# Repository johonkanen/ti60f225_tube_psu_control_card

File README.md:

# Ti60F225 control card

An FPGA control card for the tube_power_5_1 power board, built around an Efinix Titanium Ti60F225C4, designed in
KiCad 10. It is a conversion of the Agilex 3 control card (`~/dev/ti60f225_control_card`, GitHub
`agilex3_control_card`): same outline, 2×25 1.27 mm power-board header and JTAG header positions.

**Status: phase 4 of the conversion done (2026-10-30).** The schematic is converted to the Ti60F225 (ERC clean,
netlist checked by `tools/check_schematic.py`), and its FPGA ball assignment passes Efinity's Interface Designer
check and a stub compile with SPI active x4 (`efinity/pinplan/run.sh --compile`, `reference/pin_assignment.csv`). The board
(`hardware/control_card.kicad_pcb`) is still the Agilex 3 layout. Plan, decisions and remaining steps:
[`CONVERSION_PLAN.md`](CONVERSION_PLAN.md); device requirements: [`docs/ti60_requirements.md`](docs/ti60_requirements.md).

## Board

Copper layers of `hardware/control_card.kicad_pcb`, plotted by GitHub Actions on every board change
([kicad-board-plots](https://github.com/johonkanen/kicad-board-plots)).

<!-- board-plots:start -->
<!-- Generated by kicad-board-plots; edits between these markers are overwritten. -->

Copper layers of `hardware/control_card.kicad_pcb` in stack order, without silkscreen. Plotted by [kicad-board-plots](https://github.com/johonkanen/kicad-board-plots) on each board change; the images live on the `renders` branch.

<table>
<tr>
<td align="center"><br><b>F.Cu: signal (top)</b></td>
<td align="center"><br><b>In1.Cu: GND plane</b></td>
</tr>
<tr>
<td align="center"><br><b>In2.Cu: signal, +1V8 pour</b></td>
<td align="center"><br><b>In3.Cu: +0V95, +3V3 planes</b></td>
</tr>
<tr>
<td align="center"><br><b>In4.Cu: GND plane</b></td>
<td align="center"><br><b>B.Cu: signal, SW_3V3, SW_1V8, +0V95, GND, SW_0V95 and 3 more pours (bottom, seen from the top)</b></td>
</tr>
</table>

<!-- board-plots:end -->

## Repository layout

| Path | Contents |
|---|---|
| `hardware/` | KiCad project (`control_card.kicad_pro`), sheets, project libraries, JLCPCB design rules |
| `reference/ti60f225_pinout.csv` | All 225 Ti60F225 balls: pad, bank, HVIO/HSIO type, configuration function, LVDS pair, clock region |
| `reference/` | Power-board header pinout, ADC mux channel table, JLC part cache, the Agilex pin list (for net names) |
| `docs/` | JLCPCB production checklist |
| `tools/jlc/` | Submodule [jlc-tools](https://github.com/johonkanen/jlc-tools): JLC part search, stock check, BOM/CPL and Gerber export |

Clone with `git clone --recursive`, or run `git submodule update --init` after cloning.

## License

[MIT](LICENSE).

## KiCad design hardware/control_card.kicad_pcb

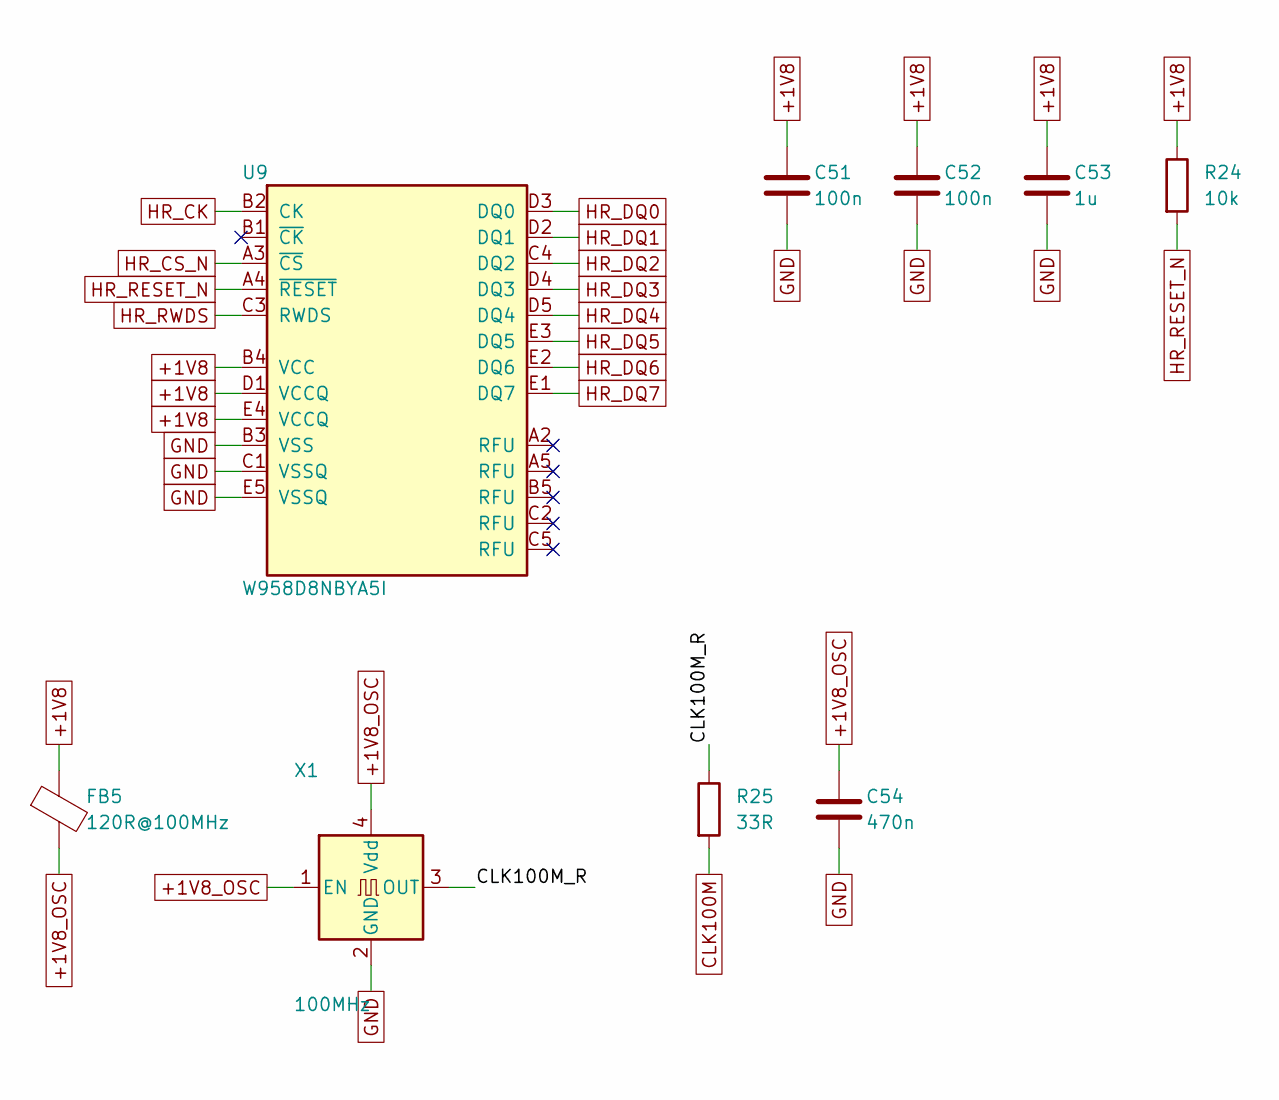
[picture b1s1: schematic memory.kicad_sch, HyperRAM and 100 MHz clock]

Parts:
C51, C52: 100n; C_0402_1005Metric; MPN CL05B104KO5NNNC; LCSC C1525
C53: 1u; C_0402_1005Metric; MPN CL05A105KA5NQNC; LCSC C52923
C54: 470n; C_0402_1005Metric; MPN CL05A474KP5NNNC; LCSC C47339
FB5: 120R@100MHz; L_0603_1608Metric; MPN BLM18PG121SN1D; LCSC C14709
R24: 10k; R_0402_1005Metric; MPN 0402WGF1002TCE; LCSC C25744
R25: 33R; R_0402_1005Metric; MPN 0402WGF330JTCE; LCSC C25105
U9: W958D8NBYA5I; BGA-24_6x8mm_Layout5x5_P1.0mm_CY0.5; MPN W958D8NBYA5I; LCSC C7420405
X1: 100MHz; Oscillator_SMD_Abracon_ASE-4Pin_3.2x2.5mm; MPN OT3225100MJBA4SL; LCSC C4353707

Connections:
+1V8: C51.1, C52.1, C53.1, FB5.1, R24.1, U9.B4 (VCC), U9.D1 (VCCQ), U9.E4 (VCCQ); also elsewhere on the board
+1V8_OSC: C54.1, FB5.2, X1.1 (EN), X1.4 (Vdd)
/HyperRAM and clock/CLK100M_R: R25.1, X1.3 (OUT)
CLK100M: R25.2; also elsewhere on the board
GND: C51.2, C52.2, C53.2, C54.2, U9.B3 (VSS), U9.C1 (VSSQ), U9.E5 (VSSQ), X1.2 (GND); also elsewhere on the board
HR_CK: U9.B2 (CK); also elsewhere on the board
HR_CS_N: U9.A3 (~CS); also elsewhere on the board
HR_DQ0: U9.D3 (DQ0); also elsewhere on the board
HR_DQ1: U9.D2 (DQ1); also elsewhere on the board
HR_DQ2: U9.C4 (DQ2); also elsewhere on the board
HR_DQ3: U9.D4 (DQ3); also elsewhere on the board
HR_DQ4: U9.D5 (DQ4); also elsewhere on the board
HR_DQ5: U9.E3 (DQ5); also elsewhere on the board
HR_DQ6: U9.E2 (DQ6); also elsewhere on the board
HR_DQ7: U9.E1 (DQ7); also elsewhere on the board
HR_RESET_N: R24.2, U9.A4 (~RESET); also elsewhere on the board
HR_RWDS: U9.C3 (RWDS); also elsewhere on the board

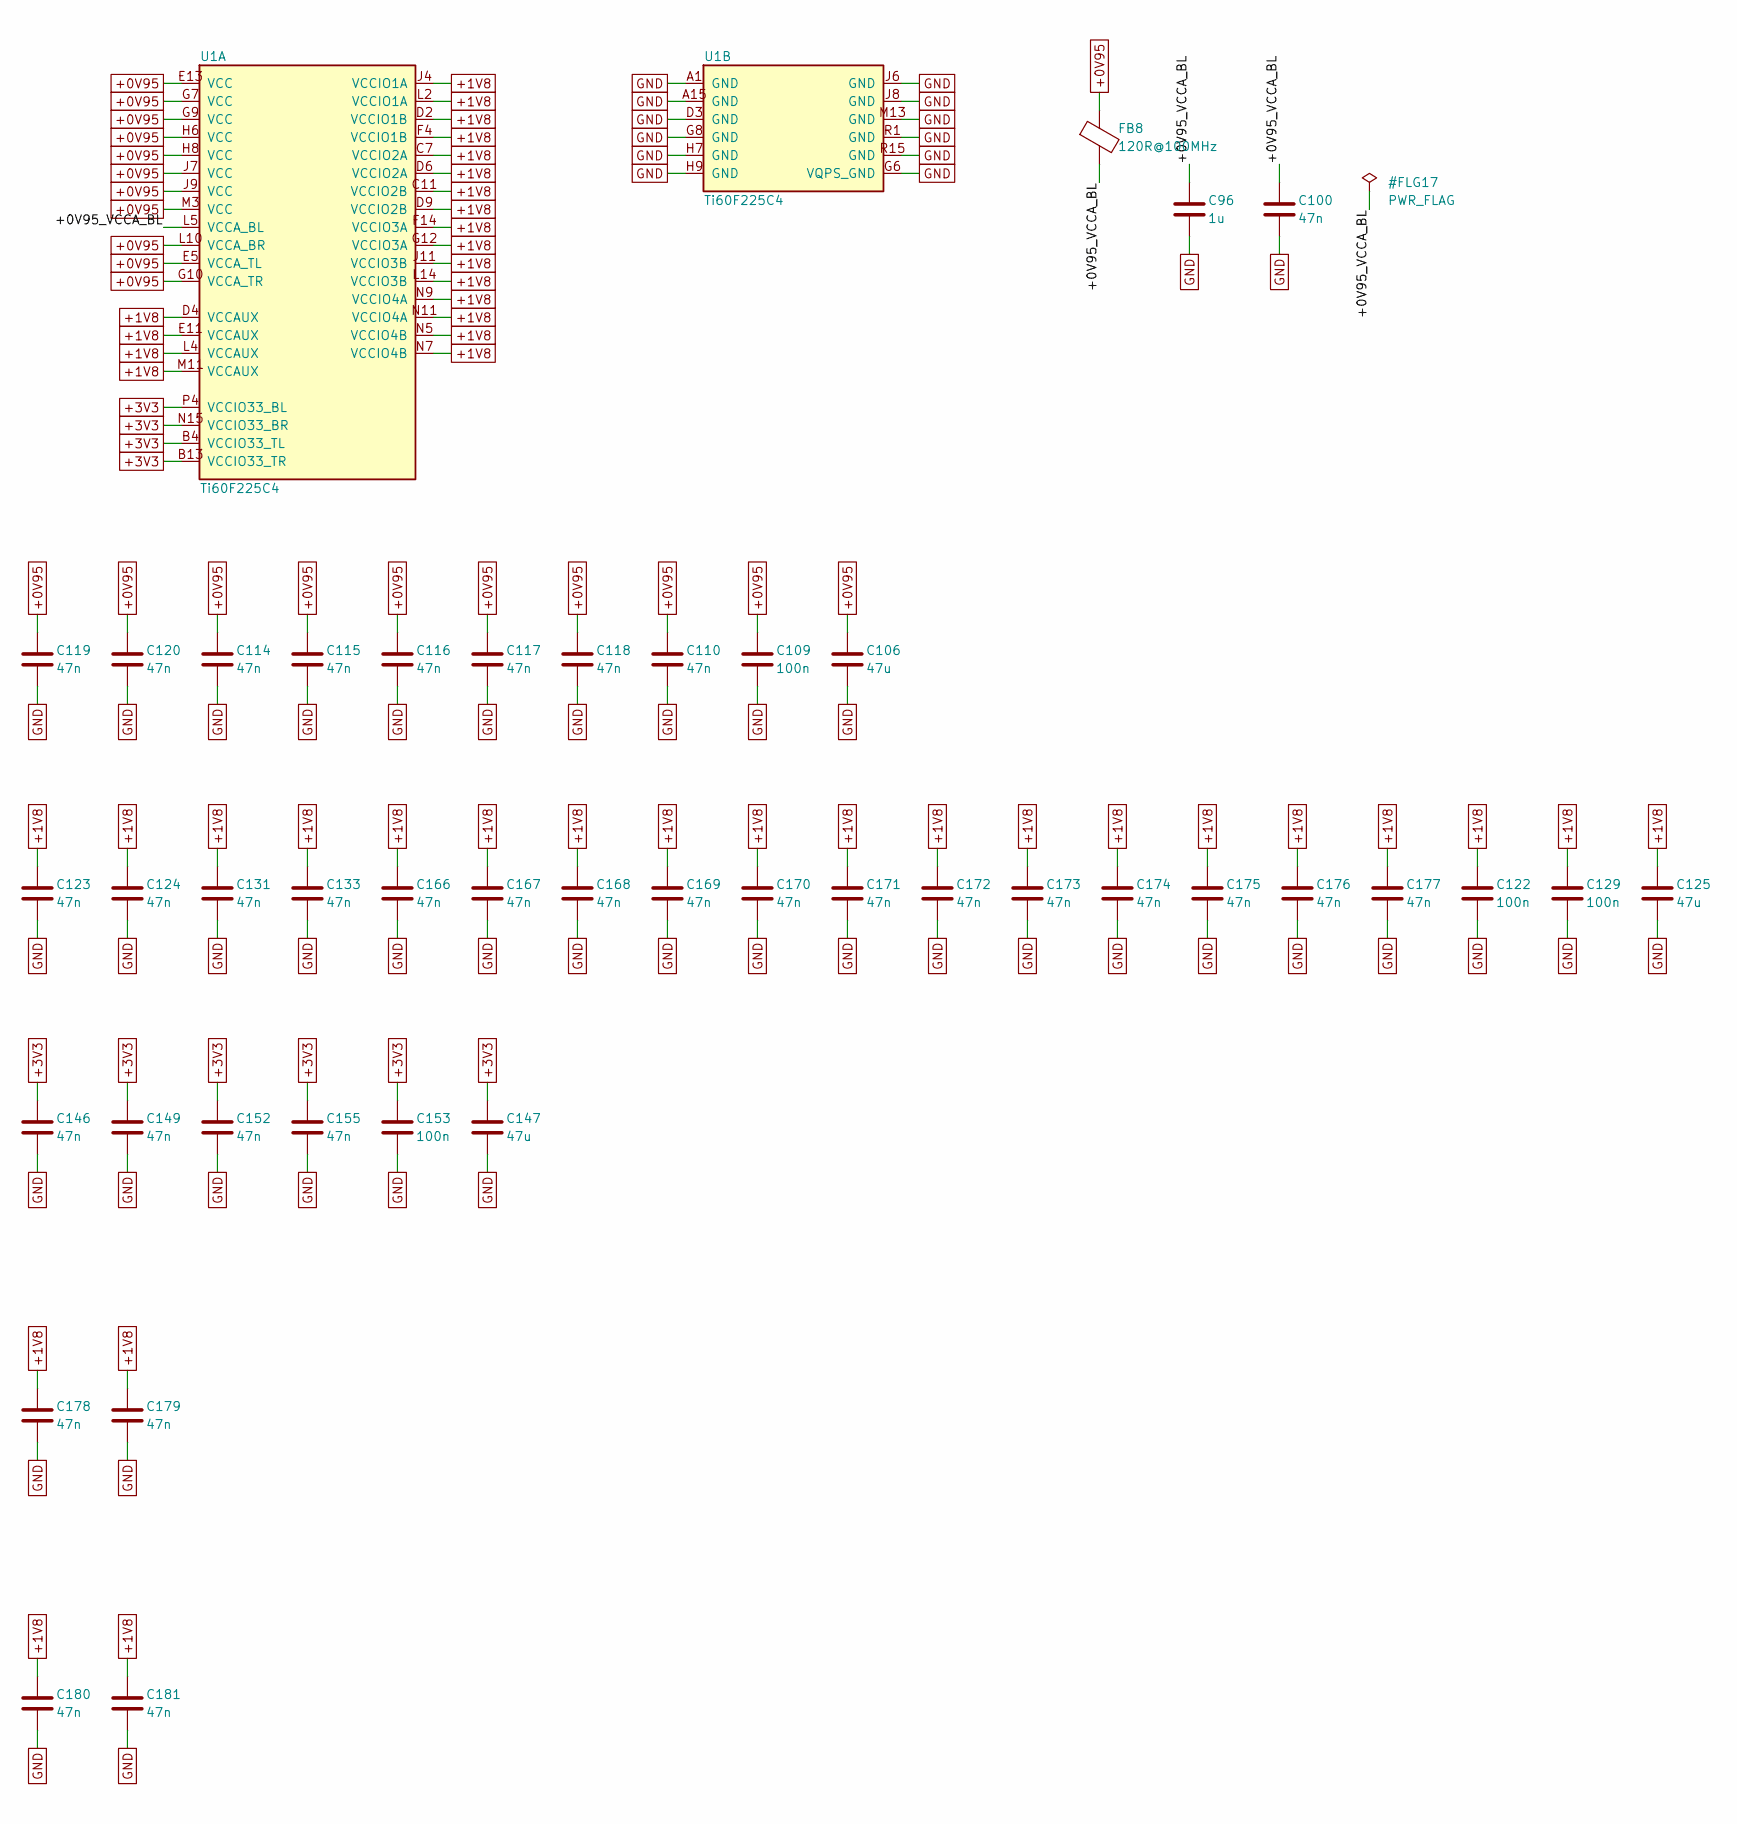
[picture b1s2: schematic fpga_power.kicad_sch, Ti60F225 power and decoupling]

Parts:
C96: 1u; C_0201_0603Metric; MPN CL03A105MQ3CSNC; LCSC C170152
C100, C110, C114, C115, C116, C117, C118, C119, C120, C123, C124, C131, C133, C146, C149, C152, C155, C166, C167, C168, C169, C170, C171, C172, C173, C174, C175, C176, C177, C178, C179, C180, C181: 47n; C_0201_0603Metric; MPN GRM033R60J473KE19D; LCSC C85925
C106, C125, C147: 47u; C_0603_1608Metric; MPN GRM188R60J476ME15D; LCSC C140782
C109, C122, C129, C153: 100n; C_0201_0603Metric; MPN CL03A104KP3NNNC; LCSC C49062
FB8: 120R@100MHz; L_0603_1608Metric; MPN BLM18PG121SN1D; LCSC C14709
U1: Ti60F225C4; Efinix_F225; MPN Ti60F225C4

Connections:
+0V95: C106.1, C109.1, C110.1, C114.1, C115.1, C116.1, C117.1, C118.1, C119.1, C120.1, FB8.1, U1.E5 (VCCA_TL), U1.E13 (VCC), U1.G7 (VCC), U1.G9 (VCC), U1.G10 (VCCA_TR), U1.H6 (VCC), U1.H8 (VCC), U1.J7 (VCC), U1.J9 (VCC), U1.L10 (VCCA_BR), U1.M3 (VCC); also elsewhere on the board
+1V8: C122.1, C123.1, C124.1, C125.1, C129.1, C131.1, C133.1, C166.1, C167.1, C168.1, C169.1, C170.1, C171.1, C172.1, C173.1, C174.1, C175.1, C176.1, C177.1, C178.1, C179.1, C180.1, C181.1, U1.C7 (VCCIO2A), U1.C11 (VCCIO2B), U1.D2 (VCCIO1B), U1.D4 (VCCAUX), U1.D6 (VCCIO2A), U1.D9 (VCCIO2B), U1.E11 (VCCAUX), U1.F4 (VCCIO1B), U1.F14 (VCCIO3A), U1.G12 (VCCIO3A), U1.J4 (VCCIO1A), U1.J11 (VCCIO3B), U1.L2 (VCCIO1A), U1.L4 (VCCAUX), U1.L14 (VCCIO3B), U1.M11 (VCCAUX), U1.N5 (VCCIO4B), U1.N7 (VCCIO4B), U1.N9 (VCCIO4A), U1.N11 (VCCIO4A); also elsewhere on the board
+3V3: C146.1, C147.1, C149.1, C152.1, C153.1, C155.1, U1.B4 (VCCIO33_TL), U1.B13 (VCCIO33_TR), U1.N15 (VCCIO33_BR), U1.P4 (VCCIO33_BL); also elsewhere on the board
/FPGA power/+0V95_VCCA_BL: C96.1, C100.1, FB8.2, U1.L5 (VCCA_BL)
GND: C96.2, C100.2, C106.2, C109.2, C110.2, C114.2, C115.2, C116.2, C117.2, C118.2, C119.2, C120.2, C122.2, C123.2, C124.2, C125.2, C129.2, C131.2, C133.2, C146.2, C147.2, C149.2, C152.2, C153.2, C155.2, C166.2, C167.2, C168.2, C169.2, C170.2, C171.2, C172.2, C173.2, C174.2, C175.2, C176.2, C177.2, C178.2, C179.2, C180.2, C181.2, U1.A1 (GND), U1.A15 (GND), U1.D3 (GND), U1.G6 (VQPS_GND), U1.G8 (GND), U1.H7 (GND), U1.H9 (GND), U1.J6 (GND), U1.J8 (GND), U1.M13 (GND), U1.R1 (GND), U1.R15 (GND); also elsewhere on the board

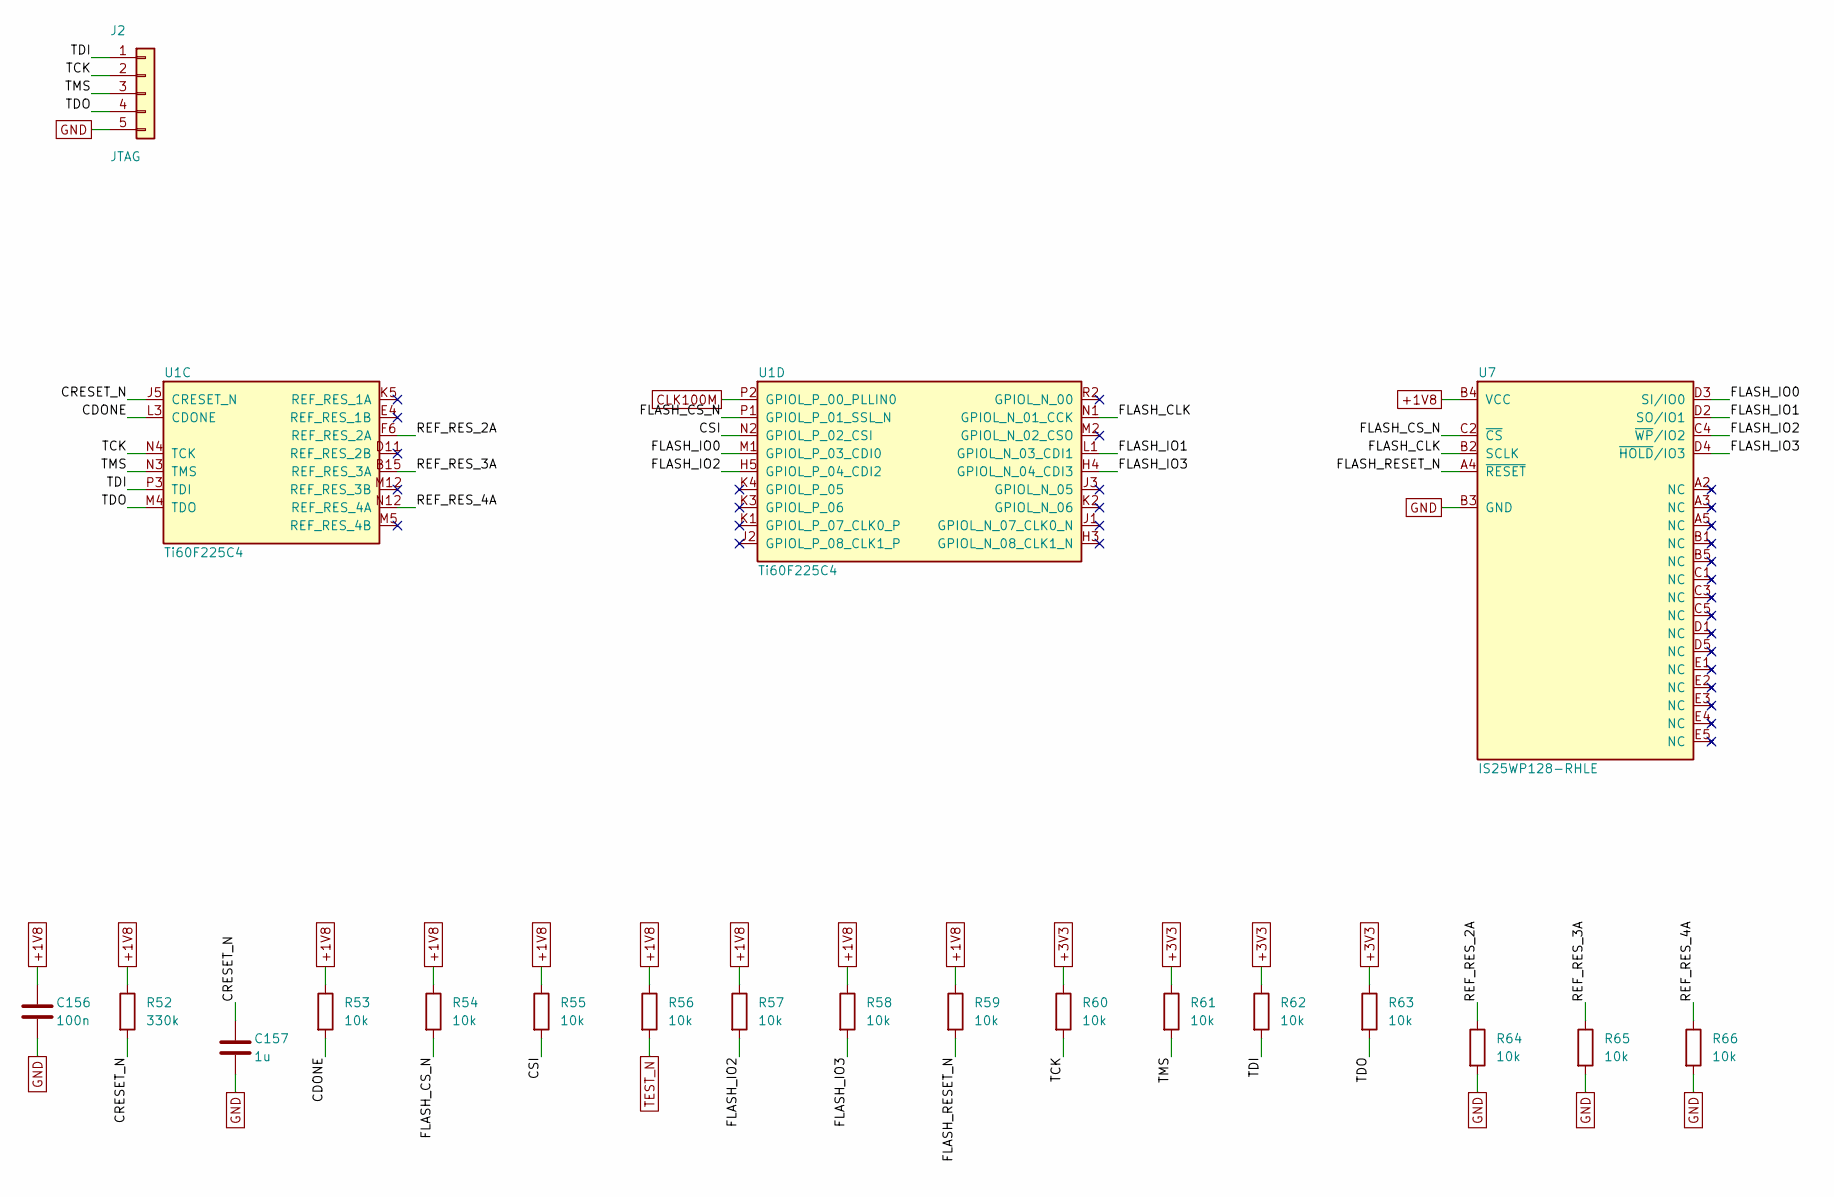
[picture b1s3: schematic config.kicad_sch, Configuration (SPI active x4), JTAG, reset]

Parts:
C156: 100n; C_0402_1005Metric; MPN CL05B104KO5NNNC; LCSC C1525
C157: 1u; C_0402_1005Metric; MPN CL05A105KA5NQNC; LCSC C52923
J2: JTAG; PinHeader_1x05_P2.54mm_Vertical
R52: 330k; R_0402_1005Metric; MPN 0402WGF3303TCE; LCSC C25778
R53, R54, R55, R56, R57, R58, R59, R60, R61, R62, R63, R64, R65, R66: 10k; R_0201_0603Metric; MPN 0201WMF1002TEE; LCSC C473048
U1: Ti60F225C4; Efinix_F225; MPN Ti60F225C4
U7: IS25WP128-RHLE; BGA-24_6x8mm_Layout5x5_P1.0mm_CY0.5; MPN IS25WP128-RHLE; LCSC C1349419

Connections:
+1V8: C156.1, R52.1, R53.1, R54.1, R55.1, R56.1, R57.1, R58.1, R59.1, U7.B4 (VCC); also elsewhere on the board
+3V3: R60.1, R61.1, R62.1, R63.1; also elsewhere on the board
/Configuration/CDONE: R53.2, U1.L3 (CDONE)
/Configuration/CRESET_N: C157.1, R52.2, U1.J5 (CRESET_N)
/Configuration/CSI: R55.2, U1.N2 (GPIOL_P_02_CSI)
/Configuration/FLASH_CLK: U1.N1 (GPIOL_N_01_CCK), U7.B2 (C)
/Configuration/FLASH_CS_N: R54.2, U1.P1 (GPIOL_P_01_SSL_N), U7.C2 (~S)
/Configuration/FLASH_IO0: U1.M1 (GPIOL_P_03_CDI0), U7.D3 (DQ0)
/Configuration/FLASH_IO1: U1.L1 (GPIOL_N_03_CDI1), U7.D2 (DQ1)
/Configuration/FLASH_IO2: R57.2, U1.H5 (GPIOL_P_04_CDI2), U7.C4 (~W/DQ2)
/Configuration/FLASH_IO3: R58.2, U1.H4 (GPIOL_N_04_CDI3), U7.D4 (~HOLD/DQ3)
/Configuration/FLASH_RESET_N: R59.2, U7.A4 (~RESET)
/Configuration/REF_RES_2A: R64.1, U1.F6 (REF_RES_2A)
/Configuration/REF_RES_3A: R65.1, U1.B15 (REF_RES_3A)
/Configuration/REF_RES_4A: R66.1, U1.N12 (REF_RES_4A)
/Configuration/TCK: J2.2, R60.2, U1.N4 (TCK)
/Configuration/TDI: J2.1, R62.2, U1.P3 (TDI)
/Configuration/TDO: J2.4, R63.2, U1.M4 (TDO)
/Configuration/TMS: J2.3, R61.2, U1.N3 (TMS)
CLK100M: U1.P2 (GPIOL_P_00_PLLIN0); also elsewhere on the board
GND: C156.2, C157.2, J2.5, R64.2, R65.2, R66.2, U7.B3 (VSS); also elsewhere on the board
TEST_N: R56.2; also elsewhere on the board

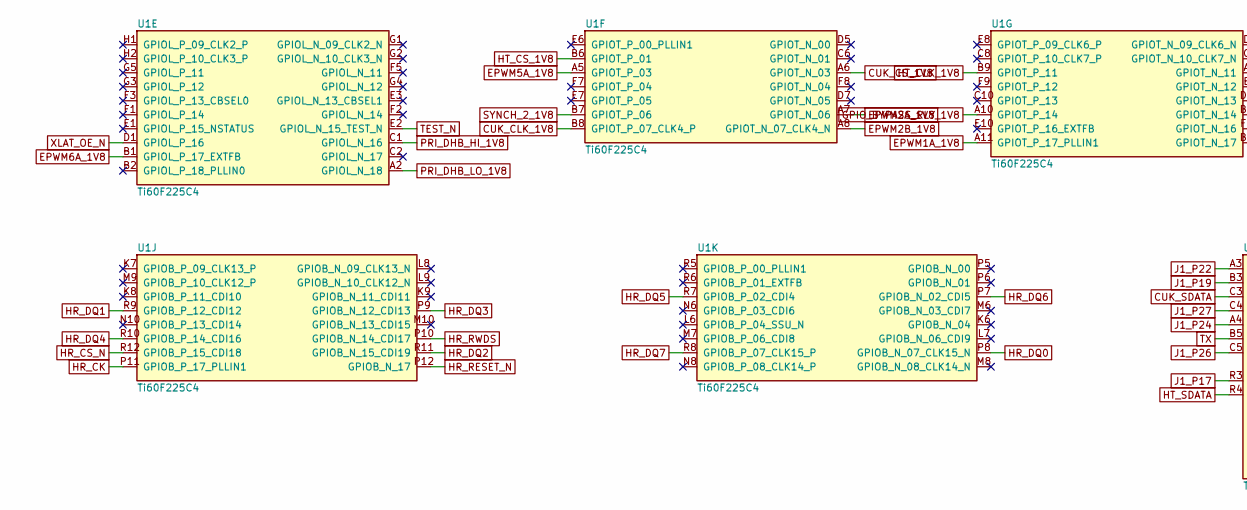
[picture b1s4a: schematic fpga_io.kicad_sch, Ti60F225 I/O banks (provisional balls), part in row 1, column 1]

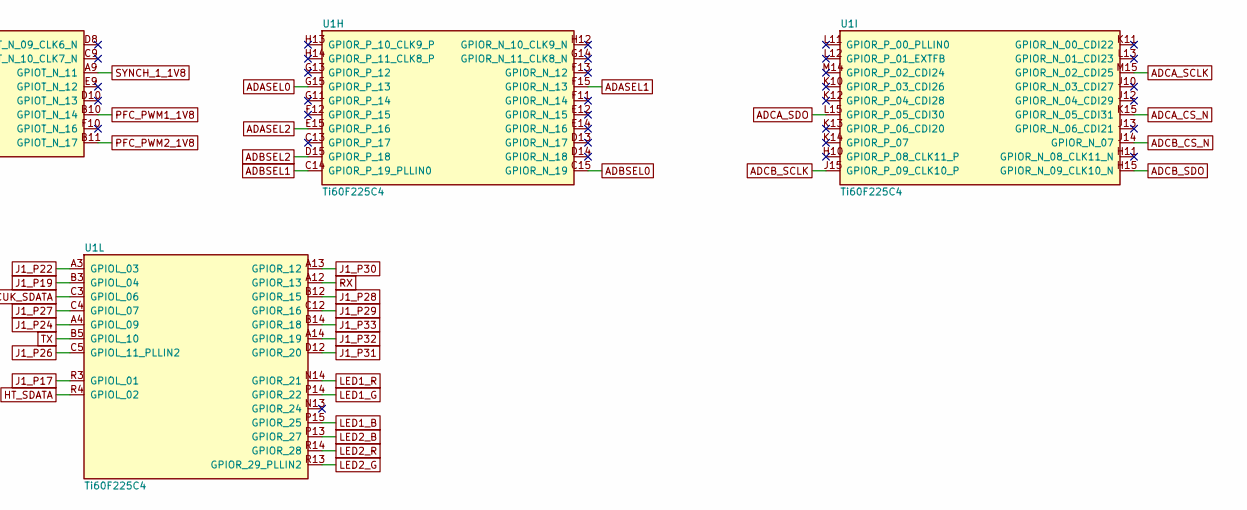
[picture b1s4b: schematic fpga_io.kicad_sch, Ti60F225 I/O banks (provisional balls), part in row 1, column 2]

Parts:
U1: Ti60F225C4; Efinix_F225; MPN Ti60F225C4

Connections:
ADASEL0: U1.G15 (GPIOR_P_13); also elsewhere on the board
ADASEL1: U1.F15 (GPIOR_N_13); also elsewhere on the board
ADASEL2: U1.E15 (GPIOR_P_16); also elsewhere on the board
ADBSEL0: U1.C15 (GPIOR_N_19); also elsewhere on the board
ADBSEL1: U1.C14 (GPIOR_P_19_PLLIN0); also elsewhere on the board
ADBSEL2: U1.D15 (GPIOR_P_18); also elsewhere on the board
ADCA_CS_N: U1.K15 (GPIOR_N_05_CDI31); also elsewhere on the board
ADCA_SCLK: U1.M15 (GPIOR_N_02_CDI25); also elsewhere on the board
ADCA_SDO: U1.L15 (GPIOR_P_05_CDI30); also elsewhere on the board
ADCB_CS_N: U1.J14 (GPIOR_N_07); also elsewhere on the board
ADCB_SCLK: U1.J15 (GPIOR_P_09_CLK10_P); also elsewhere on the board
ADCB_SDO: U1.H15 (GPIOR_N_09_CLK10_N); also elsewhere on the board
CUK_CLK_1V8: U1.B8 (GPIOT_P_07_CLK4_P); also elsewhere on the board
CUK_CS_1V8: U1.A6 (GPIOT_N_03); also elsewhere on the board
CUK_SDATA: U1.C3 (GPIOL_06); also elsewhere on the board
EPWM1A_1V8: U1.A11 (GPIOT_P_17_PLLIN1); also elsewhere on the board
EPWM2A_1V8: U1.A7 (GPIOT_N_06); also elsewhere on the board
EPWM2B_1V8: U1.A8 (GPIOT_N_07_CLK4_N); also elsewhere on the board
EPWM5A_1V8: U1.A5 (GPIOT_P_03); also elsewhere on the board
EPWM6A_1V8: U1.B1 (GPIOL_P_17_EXTFB); also elsewhere on the board
GPIO_BYPASS_RLY_1V8: U1.A10 (GPIOT_P_14); also elsewhere on the board
HR_CK: U1.P11 (GPIOB_P_17_PLLIN1); also elsewhere on the board
HR_CS_N: U1.R12 (GPIOB_P_15_CDI18); also elsewhere on the board
HR_DQ0: U1.P8 (GPIOB_N_07_CLK15_N); also elsewhere on the board
HR_DQ1: U1.R9 (GPIOB_P_12_CDI12); also elsewhere on the board
HR_DQ2: U1.R11 (GPIOB_N_15_CDI19); also elsewhere on the board
HR_DQ3: U1.P9 (GPIOB_N_12_CDI13); also elsewhere on the board
HR_DQ4: U1.R10 (GPIOB_P_14_CDI16); also elsewhere on the board
HR_DQ5: U1.R7 (GPIOB_P_02_CDI4); also elsewhere on the board
HR_DQ6: U1.P7 (GPIOB_N_02_CDI5); also elsewhere on the board
HR_DQ7: U1.R8 (GPIOB_P_07_CLK15_P); also elsewhere on the board
HR_RESET_N: U1.P12 (GPIOB_N_17); also elsewhere on the board
HR_RWDS: U1.P10 (GPIOB_N_14_CDI17); also elsewhere on the board
HT_CLK_1V8: U1.B9 (GPIOT_P_11); also elsewhere on the board
HT_CS_1V8: U1.B6 (GPIOT_P_01); also elsewhere on the board
HT_SDATA: U1.R4 (GPIOL_02); also elsewhere on the board
J1_P17: U1.R3 (GPIOL_01); also elsewhere on the board
J1_P19: U1.B3 (GPIOL_04); also elsewhere on the board
J1_P22: U1.A3 (GPIOL_03); also elsewhere on the board
J1_P24: U1.A4 (GPIOL_09); also elsewhere on the board
J1_P26: U1.C5 (GPIOL_11_PLLIN2); also elsewhere on the board
J1_P27: U1.C4 (GPIOL_07); also elsewhere on the board
J1_P28: U1.B12 (GPIOR_15); also elsewhere on the board
J1_P29: U1.C12 (GPIOR_16); also elsewhere on the board
J1_P30: U1.A13 (GPIOR_12); also elsewhere on the board
J1_P31: U1.D12 (GPIOR_20); also elsewhere on the board
J1_P32: U1.A14 (GPIOR_19); also elsewhere on the board
J1_P33: U1.B14 (GPIOR_18); also elsewhere on the board
LED1_B: U1.P15 (GPIOR_25); also elsewhere on the board
LED1_G: U1.P14 (GPIOR_22); also elsewhere on the board
LED1_R: U1.N14 (GPIOR_21); also elsewhere on the board
LED2_B: U1.P13 (GPIOR_27); also elsewhere on the board
LED2_G: U1.R13 (GPIOR_29_PLLIN2); also elsewhere on the board
LED2_R: U1.R14 (GPIOR_28); also elsewhere on the board
PFC_PWM1_1V8: U1.B10 (GPIOT_N_14); also elsewhere on the board
PFC_PWM2_1V8: U1.B11 (GPIOT_N_17); also elsewhere on the board
PRI_DHB_HI_1V8: U1.C1 (GPIOL_N_16); also elsewhere on the board
PRI_DHB_LO_1V8: U1.A2 (GPIOL_N_18); also elsewhere on the board
RX: U1.A12 (GPIOR_13); also elsewhere on the board
SYNCH_1_1V8: U1.A9 (GPIOT_N_11); also elsewhere on the board
SYNCH_2_1V8: U1.B7 (GPIOT_P_06); also elsewhere on the board
TEST_N: U1.E2 (GPIOL_N_15_TEST_N); also elsewhere on the board
TX: U1.B5 (GPIOL_10); also elsewhere on the board
XLAT_OE_N: U1.D1 (GPIOL_P_16); also elsewhere on the board

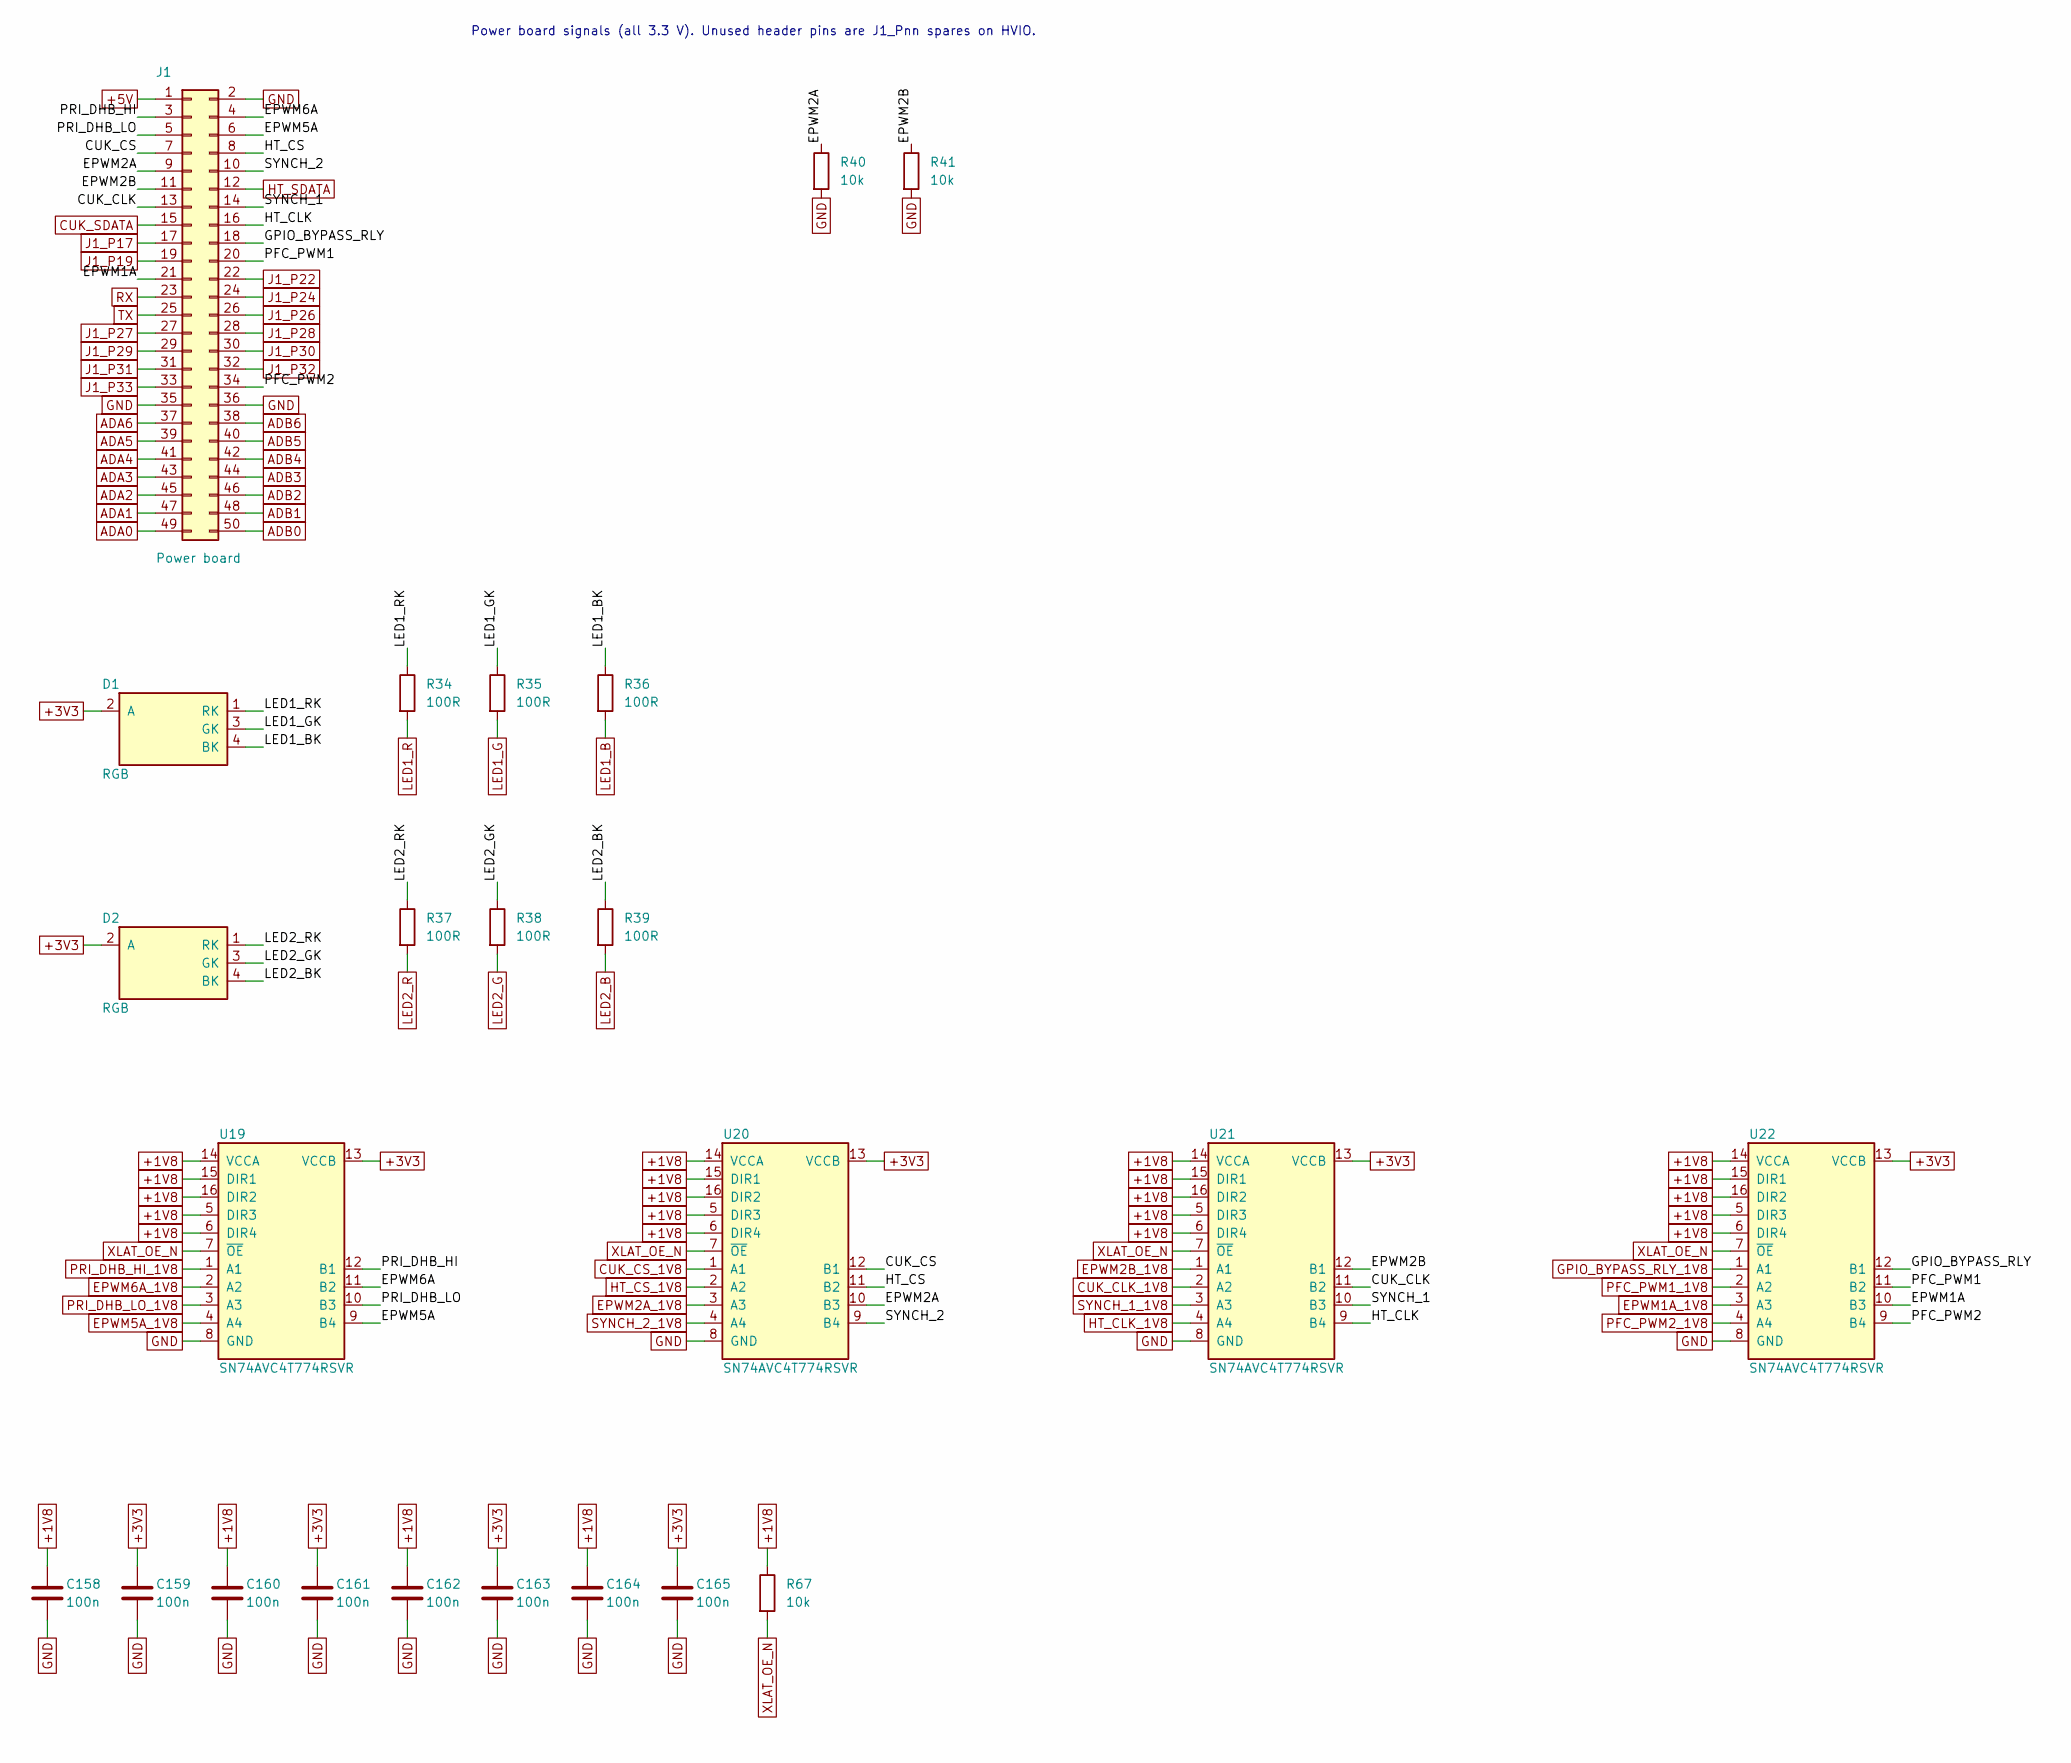
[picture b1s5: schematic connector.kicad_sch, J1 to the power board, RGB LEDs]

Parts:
C158, C159, C160, C161, C162, C163, C164, C165: 100n; C_0201_0603Metric; MPN CL03A104KP3NNNC; LCSC C49062
D1, D2: RGB; LED_RGB_APFA3010_RightAngle; MPN APFA3010LSEEZGKQBKC; LCSC C5393554
J1: Power board; PinHeader_2x25_P1.27mm_Horizontal_U25
R34, R35, R36, R37, R38, R39: 100R; R_0402_1005Metric; MPN 0402WGF1000TCE; LCSC C25076
R40, R41, R67: 10k; R_0201_0603Metric; MPN 0201WMF1002TEE; LCSC C473048
U19, U20, U21, U22: SN74AVC4T774RSVR; UQFN-16_1.8x2.6mm_P0.4mm; MPN SN74AVC4T774RSVR; LCSC C779392

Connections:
+1V8: C158.1, C160.1, C162.1, C164.1, R67.1, U19.5 (DIR3), U19.6 (DIR4), U19.14 (VCCA), U19.15 (DIR1), U19.16 (DIR2), U20.5 (DIR3), U20.6 (DIR4), U20.14 (VCCA), U20.15 (DIR1), U20.16 (DIR2), U21.5 (DIR3), U21.6 (DIR4), U21.14 (VCCA), U21.15 (DIR1), U21.16 (DIR2), U22.5 (DIR3), U22.6 (DIR4), U22.14 (VCCA), U22.15 (DIR1), U22.16 (DIR2); also elsewhere on the board
+3V3: C159.1, C161.1, C163.1, C165.1, D1.2 (A), D2.2 (A), U19.13 (VCCB), U20.13 (VCCB), U21.13 (VCCB), U22.13 (VCCB); also elsewhere on the board
+5V: J1.1; also elsewhere on the board
/Header and LEDs/CUK_CLK: J1.13, U21.11 (B2)
/Header and LEDs/CUK_CS: J1.7, U20.12 (B1)
/Header and LEDs/EPWM1A: J1.21, U22.10 (B3)
/Header and LEDs/EPWM2A: J1.9, R40.1, U20.10 (B3)
/Header and LEDs/EPWM2B: J1.11, R41.1, U21.12 (B1)
/Header and LEDs/EPWM5A: J1.6, U19.9 (B4)
/Header and LEDs/EPWM6A: J1.4, U19.11 (B2)
/Header and LEDs/GPIO_BYPASS_RLY: J1.18, U22.12 (B1)
/Header and LEDs/HT_CLK: J1.16, U21.9 (B4)
/Header and LEDs/HT_CS: J1.8, U20.11 (B2)
/Header and LEDs/LED1_BK: D1.4 (BK), R36.1
/Header and LEDs/LED1_GK: D1.3 (GK), R35.1
/Header and LEDs/LED1_RK: D1.1 (RK), R34.1
/Header and LEDs/LED2_BK: D2.4 (BK), R39.1
/Header and LEDs/LED2_GK: D2.3 (GK), R38.1
/Header and LEDs/LED2_RK: D2.1 (RK), R37.1
/Header and LEDs/PFC_PWM1: J1.20, U22.11 (B2)
/Header and LEDs/PFC_PWM2: J1.34, U22.9 (B4)
/Header and LEDs/PRI_DHB_HI: J1.3, U19.12 (B1)
/Header and LEDs/PRI_DHB_LO: J1.5, U19.10 (B3)
/Header and LEDs/SYNCH_1: J1.14, U21.10 (B3)
/Header and LEDs/SYNCH_2: J1.10, U20.9 (B4)
ADA0: J1.49; also elsewhere on the board
ADA1: J1.47; also elsewhere on the board
ADA2: J1.45; also elsewhere on the board
ADA3: J1.43; also elsewhere on the board
ADA4: J1.41; also elsewhere on the board
ADA5: J1.39; also elsewhere on the board
ADA6: J1.37; also elsewhere on the board
ADB0: J1.50; also elsewhere on the board
ADB1: J1.48; also elsewhere on the board
ADB2: J1.46; also elsewhere on the board
ADB3: J1.44; also elsewhere on the board
ADB4: J1.42; also elsewhere on the board
ADB5: J1.40; also elsewhere on the board
ADB6: J1.38; also elsewhere on the board
CUK_CLK_1V8: U21.2 (A2); also elsewhere on the board
CUK_CS_1V8: U20.1 (A1); also elsewhere on the board
CUK_SDATA: J1.15; also elsewhere on the board
EPWM1A_1V8: U22.3 (A3); also elsewhere on the board
EPWM2A_1V8: U20.3 (A3); also elsewhere on the board
EPWM2B_1V8: U21.1 (A1); also elsewhere on the board
EPWM5A_1V8: U19.4 (A4); also elsewhere on the board
EPWM6A_1V8: U19.2 (A2); also elsewhere on the board
GND: C158.2, C159.2, C160.2, C161.2, C162.2, C163.2, C164.2, C165.2, J1.2, J1.35, J1.36, R40.2, R41.2, U19.8 (GND), U20.8 (GND), U21.8 (GND), U22.8 (GND); also elsewhere on the board
GPIO_BYPASS_RLY_1V8: U22.1 (A1); also elsewhere on the board
HT_CLK_1V8: U21.4 (A4); also elsewhere on the board
HT_CS_1V8: U20.2 (A2); also elsewhere on the board
HT_SDATA: J1.12; also elsewhere on the board
J1_P17: J1.17; also elsewhere on the board
J1_P19: J1.19; also elsewhere on the board
J1_P22: J1.22; also elsewhere on the board
J1_P24: J1.24; also elsewhere on the board
J1_P26: J1.26; also elsewhere on the board
J1_P27: J1.27; also elsewhere on the board
J1_P28: J1.28; also elsewhere on the board
J1_P29: J1.29; also elsewhere on the board
J1_P30: J1.30; also elsewhere on the board
J1_P31: J1.31; also elsewhere on the board
J1_P32: J1.32; also elsewhere on the board
J1_P33: J1.33; also elsewhere on the board
LED1_B: R36.2; also elsewhere on the board
LED1_G: R35.2; also elsewhere on the board
LED1_R: R34.2; also elsewhere on the board
LED2_B: R39.2; also elsewhere on the board
LED2_G: R38.2; also elsewhere on the board
LED2_R: R37.2; also elsewhere on the board
PFC_PWM1_1V8: U22.2 (A2); also elsewhere on the board
PFC_PWM2_1V8: U22.4 (A4); also elsewhere on the board
PRI_DHB_HI_1V8: U19.1 (A1); also elsewhere on the board
PRI_DHB_LO_1V8: U19.3 (A3); also elsewhere on the board
RX: J1.23; also elsewhere on the board
SYNCH_1_1V8: U21.3 (A3); also elsewhere on the board
SYNCH_2_1V8: U20.4 (A4); also elsewhere on the board
TX: J1.25; also elsewhere on the board
XLAT_OE_N: R67.2, U19.7 (~OE), U20.7 (~OE), U21.7 (~OE), U22.7 (~OE); also elsewhere on the board

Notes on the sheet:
Power board signals (all 3.3 V). Unused header pins are J1_Pnn spares on HVIO.
